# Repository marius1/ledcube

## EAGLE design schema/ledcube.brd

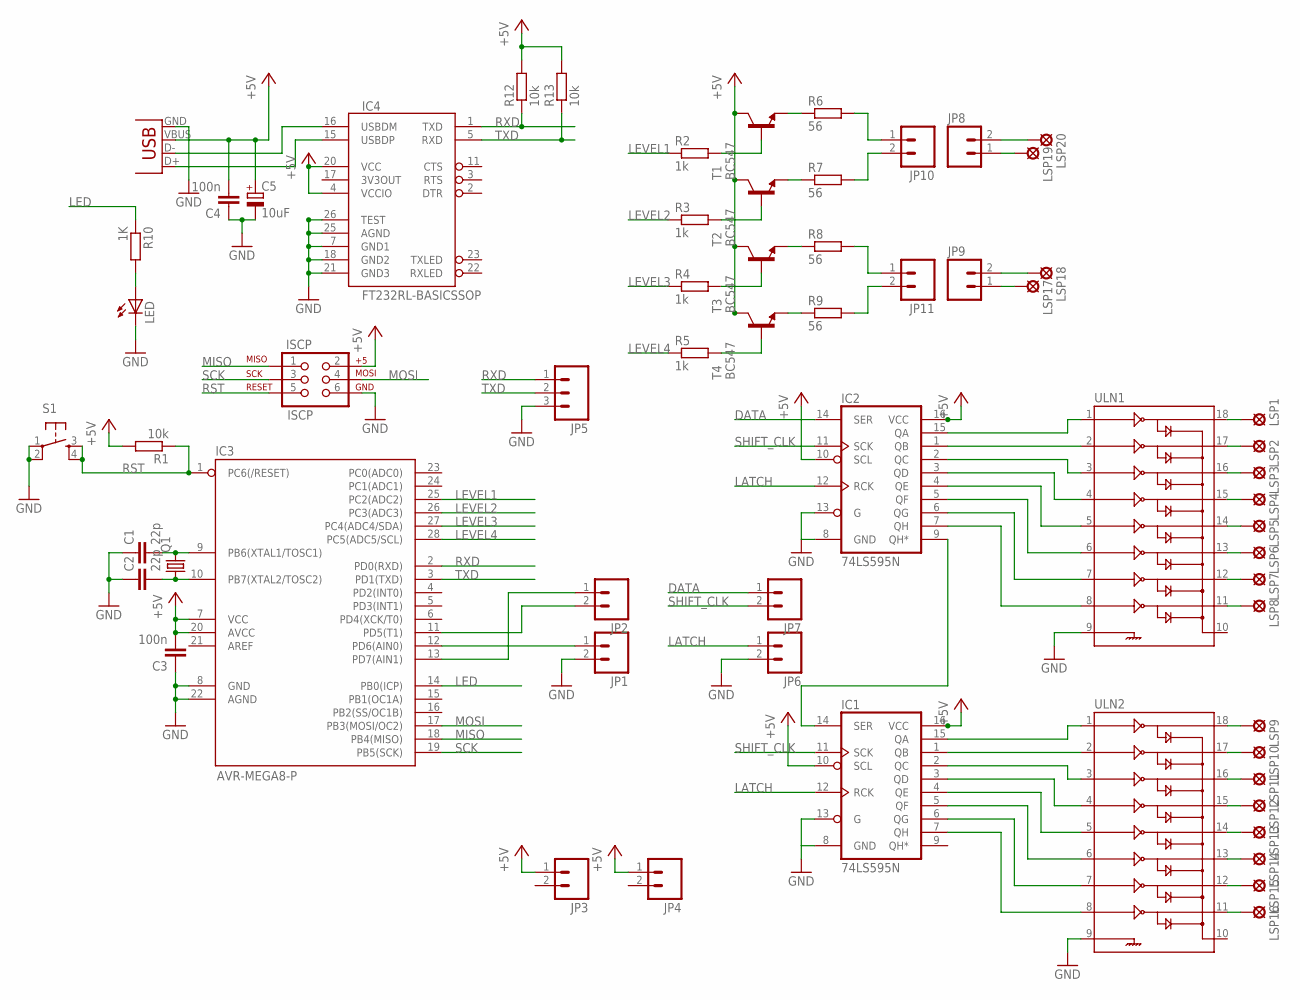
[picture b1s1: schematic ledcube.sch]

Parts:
C1, C2: 22p; C050-024X044
C3, C4: 100n; C050-024X044
C5: 10uF; E2,5-6
IC1, IC2: 74LS595N; DIL16
IC3: AVR-MEGA8-P; DIL28-3
IC4: FT232RL-BASICSSOP; SSOP28DB
ISCP: ISCP; 2X3-NS
JP1, JP2, JP3, JP4, JP6, JP7, JP8, JP9, JP10, JP11: M02PTH3; 1X02_LONGPADS
JP5: M03PTH; 1X03
LED: LED3MM
LSP1, LSP2, LSP3, LSP4, LSP5, LSP6, LSP7, LSP8, LSP9, LSP10, LSP11, LSP12, LSP13, LSP14, LSP15, LSP16, LSP17, LSP18, LSP19, LSP20: LSP10
Q1: CRYSTALHC49S; HC49/S
R1, R12, R13: 10k; 0204V
R2, R3, R4, R5: 1k; 0204V
R6, R7, R8, R9: 56; 0204V
R10: 1K; 0204V
S1: TAC_SWITCHPTH; TACTILE-PTH
T1, T2, T3, T4: BC547; TO92
ULN1, ULN2: ULN2803DIP; DIL18
X1: USBSMD; USB-MINIB

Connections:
+5V: C3.2, C4.2, C5.+, IC1.10 (SCL), IC1.16 (VCC), IC2.10 (SCL), IC2.16 (VCC), IC3.7 (VCC), IC3.20 (AVCC), IC4.4 (VCCIO), IC4.20 (VCC), ISCP.2, JP3.1, JP4.1, R1.2, R12.2, R13.2, T1.3 (C), T2.3 (C), T3.3 (C), T4.3 (C), X1.VBUS
DATA: IC2.14 (SER), JP7.1
GND: C1.1, C2.1, C3.1, C4.1, C5.-, IC1.8 (GND), IC1.13 (G), IC2.8 (GND), IC2.13 (G), IC3.8 (GND), IC3.22 (AGND), IC4.7 (GND1), IC4.18 (GND2), IC4.21 (GND3), IC4.25 (AGND), IC4.26 (TEST), ISCP.6, JP1.2, JP5.3, JP6.2, LED.K (C), S1.1, S1.2, ULN1.9, ULN2.9, X1.GND
LATCH: IC1.12 (RCK), IC2.12 (RCK), JP6.1
LED: IC3.14 (PB0(ICP)), R10.1
LEVEL1: IC3.25 (PC2(ADC2)), R2.1
LEVEL2: IC3.26 (PC3(ADC3)), R3.1
LEVEL3: IC3.27 (PC4(ADC4/SDA)), R4.1
LEVEL4: IC3.28 (PC5(ADC5/SCL)), R5.1
MISO: IC3.18 (PB4(MISO)), ISCP.1
MOSI: IC3.17 (PB3(MOSI/OC2)), ISCP.4
unnamed: R6.1, T1.1 (E)
unnamed: R7.1, T2.1 (E)
unnamed: R8.1, T3.1 (E)
unnamed: R9.1, T4.1 (E)
unnamed: R5.2, T4.2 (B)
unnamed: R4.2, T3.2 (B)
unnamed: R3.2, T2.2 (B)
unnamed: R2.2, T1.2 (B)
unnamed: C2.2, IC3.10 (PB7(XTAL2/TOSC2)), Q1.1
unnamed: C1.2, IC3.9 (PB6(XTAL1/TOSC1)), Q1.2
unnamed: JP10.1, R6.2
unnamed: IC4.16 (USBDM), X1.D-
unnamed: IC4.15 (USBDP), X1.D+
unnamed: IC1.15 (QA), ULN2.1
unnamed: IC1.1 (QB), ULN2.2
unnamed: IC1.2 (QC), ULN2.3
unnamed: IC1.3 (QD), ULN2.4
unnamed: IC1.4 (QE), ULN2.5
unnamed: IC1.5 (QF), ULN2.6
unnamed: IC1.6 (QG), ULN2.7
unnamed: IC1.7 (QH), ULN2.8
unnamed: IC2.15 (QA), ULN1.1
unnamed: IC2.1 (QB), ULN1.2
unnamed: IC2.2 (QC), ULN1.3
unnamed: IC2.3 (QD), ULN1.4
unnamed: IC2.4 (QE), ULN1.5
unnamed: IC2.5 (QF), ULN1.6
unnamed: IC2.6 (QG), ULN1.7
unnamed: IC2.7 (QH), ULN1.8
unnamed: JP9.1, LSP17.MP
unnamed: JP11.1, R8.2
unnamed: JP11.2, R9.2
unnamed: IC3.11 (PD5(T1)), JP2.2
unnamed: IC3.12 (PD6(AIN0)), JP1.1
unnamed: IC3.13 (PD7(AIN1)), JP2.1
unnamed: JP10.2, R7.2
unnamed: JP9.2, LSP18.MP
unnamed: JP8.1, LSP19.MP
unnamed: JP8.2, LSP20.MP
unnamed: LSP16.MP, ULN2.11
unnamed: LSP15.MP, ULN2.12
unnamed: LSP14.MP, ULN2.13
unnamed: LSP13.MP, ULN2.14
unnamed: LSP12.MP, ULN2.15
unnamed: LSP11.MP, ULN2.16
unnamed: LSP10.MP, ULN2.17
unnamed: LSP9.MP, ULN2.18
unnamed: IC1.14 (SER), IC2.9 (QH*)
unnamed: LED.A, R10.2
unnamed: LSP8.MP, ULN1.11
unnamed: LSP1.MP, ULN1.18
unnamed: LSP7.MP, ULN1.12
unnamed: LSP6.MP, ULN1.13
unnamed: LSP5.MP, ULN1.14
unnamed: LSP4.MP, ULN1.15
unnamed: LSP3.MP, ULN1.16
unnamed: LSP2.MP, ULN1.17
RST: IC3.1 (PC6(/RESET)), ISCP.5, R1.1, S1.3, S1.4
RXD: IC3.2 (PD0(RXD)), IC4.1 (TXD), JP5.1, R12.1
SCK: IC3.19 (PB5(SCK)), ISCP.3
SHIFT_CLK: IC1.11 (SCK), IC2.11 (SCK), JP7.2
TXD: IC3.3 (PD1(TXD)), IC4.5 (RXD), JP5.2, R13.1

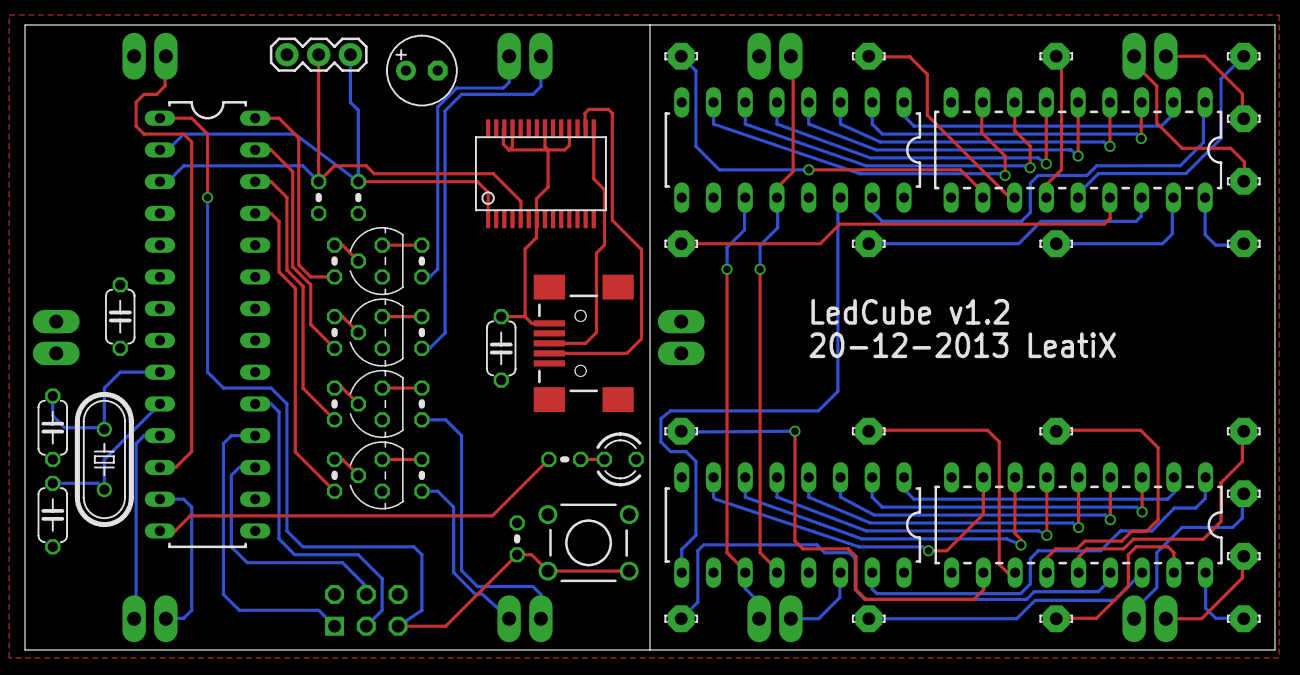
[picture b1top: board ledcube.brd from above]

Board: 4 copper layers, 100.0 x 50.0 mm, 63 parts (0 on the bottom side), 73 nets.

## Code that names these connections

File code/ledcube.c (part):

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
#include "uart/uart.h"

#define CLK_PIN 		PD5
#define CLK_PORT 		PORTD
#define CLK_DDR 		DDRD

#define DATA_PIN 		PD7
#define DATA_PORT 		PORTD
#define DATA_DDR 		DDRD

#define LATCH_PIN		PD6
#define LATCH_PORT 		PORTD
#define LATCH_DDR 		DDRD

#define LEVEL0_PIN		PC3
#define LEVEL1_PIN		PC2
#define LEVEL2_PIN		PC5
#define LEVEL3_PIN		PC4
#define LEVEL_PORT		PORTC
#define LEVEL_DDR		DDRC

#define latch_high()	LATCH_PORT |= ( 1 << PD6 )
#define latch_low()		LATCH_PORT &= ~( 1 << PD6 )

#define clk_high()		CLK_PORT |= ( 1 << PD5 )
#define clk_low()		CLK_PORT &= ~( 1 << PD5 )

#define data_high()		DATA_PORT |= ( 1 << PD7 )
#define data_low()		DATA_PORT &= ~( 1 << PD7 )

#define STATUS_LED_PIN 		PB0
#define STATUS_LED_PORT 	PORTB
#define STATUS_LED_DDR 		DDRB

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void toggleLevel( uint8_t level ) {
	
	LEVEL_PORT &= ~(1<<LEVEL0_PIN);
	LEVEL_PORT &= ~(1<<LEVEL1_PIN);
	LEVEL_PORT &= ~(1<<LEVEL2_PIN);
	LEVEL_PORT &= ~(1<<LEVEL3_PIN);
	
	switch(level) {
		case 0:
			LEVEL_PORT |= (1<<LEVEL0_PIN);
			break;
		case 1:
			LEVEL_PORT |= (1<<LEVEL1_PIN);
			break;
		case 2:
			LEVEL_PORT |= (1<<LEVEL2_PIN);
			break;
		case 3:
			LEVEL_PORT |= (1<<LEVEL3_PIN);
			break;
	}
}
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void pins_init()
{
	CLK_DDR		|= (1 << CLK_PIN);
	LATCH_DDR 	|= (1 << LATCH_PIN);	
	DATA_DDR 	|= (1 << DATA_PIN);	
	LEVEL_DDR 	|= (1 << LEVEL0_PIN) | (1 << LEVEL1_PIN) | (1 << LEVEL2_PIN) | (1 << LEVEL3_PIN);
}

void shiftOut(uint8_t val)
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
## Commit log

2013-12-20 History
2014-06-30 BOM added
2014-06-30 Schema bug updated
